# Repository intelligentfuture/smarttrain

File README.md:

# smarttrain
Software Project
- Conan
- Dome
- Neng
- Arm
- Ice
- Nami

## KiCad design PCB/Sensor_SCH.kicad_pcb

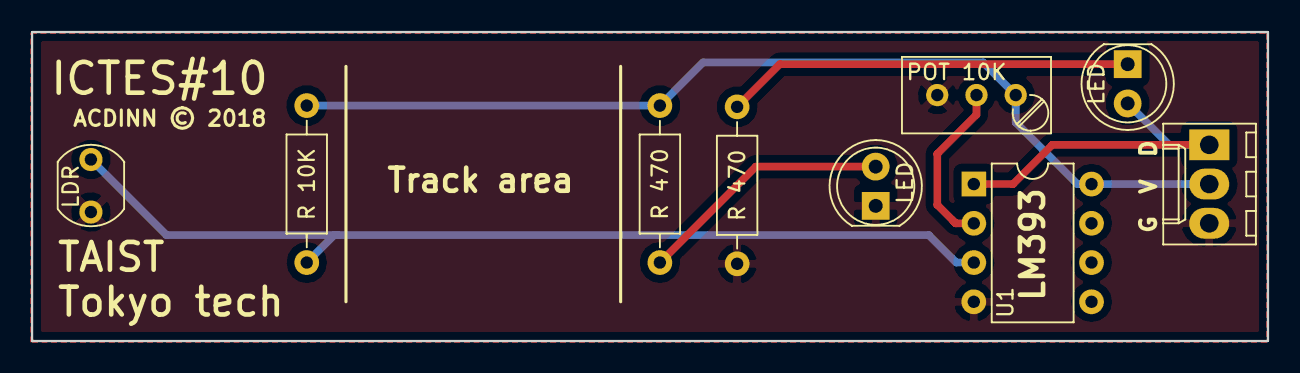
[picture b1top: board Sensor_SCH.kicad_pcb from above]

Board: 2 copper layers, 80.0 x 20.0 mm, 9 parts (0 on the bottom side), 7 nets.

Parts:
G  V  D: Conn_01x03; Molex_KK-6410-03_03x2.54mm_Straight
LDR: LDR07; Resistor_LDR_5.1x4.3_RM3.4
LED: LED; LED_D5.0mm
LED#2: LED; LED_D5.0mm
POT 10K: POT; Potentiometer_Trimmer_Bourns_3296W
R 10K, R 470, R 470#2: R; R_Axial_DIN0207_L6.3mm_D2.5mm_P10.16mm_Horizontal
U1: LM393; DIP-8_W7.62mm

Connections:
/Data: G V D.1, LED#2.2, U1.1
/GND: G V D.3, LDR.2, LED.1, POT 10K.3, R 470#2.2, U1.4
/Vcc: G V D.2, POT 10K.1, R 10K.1, R 470.1, U1.8
unnamed: LED.2, R 470.2
unnamed: LED#2.1, R 470#2.1
unnamed: LDR.1, R 10K.2
unnamed: POT 10K.2, U1.2

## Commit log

2018-03-19 init project
2018-03-19 update multipoll
2018-03-19 change boardrate
2018-03-19 remove empty line
2018-03-19 change debug msg
2018-03-19 update store
2018-03-19 change updateDB to multinode support
2018-03-19 add while to call updateDB()
2018-03-19 updateDB() -json dumps before sending
2018-03-19 clean print
2018-03-20 multiple node reader
2018-03-20 printout modbus
2018-03-20 check modbus
2018-03-20 change brate to 57600
2018-03-20 change read method for RS485
2018-03-20 print resp at update
2018-03-26 update many things, much more than i can remember, haha
2018-03-26 add sourcecode of mbed
2018-03-26 update store.py, add service /api/active , /api/timetable and /api/seed
2018-03-27 organize files
2018-04-18 Add PCB file
2018-04-18 add arduino ESP code for station node
2018-04-18 add micropython ESP code for gateway node
2018-04-18 commit before sleep
2018-04-19 FIX bug, improve performance, and more hidden bug.
2018-04-21 make data to dict
2018-04-25 Initial v2 with NTP include in each node
2018-04-25 add files
2018-04-25 ESP8266 with NTP sync
2018-04-25 update GW
2018-04-27 change esp to 6 pin and many many many fix
2018-04-28 remove delay
2018-04-28 add timetable calculator
2018-04-28 add example files .list
2018-04-30 edit node
2018-04-30 thread test
2018-04-30 add caltimetable
2018-04-30 add socket shutdown
2018-05-01 add calculate table (cal22.py)
2018-05-01 add timetable service
2018-05-01 change pin order
2018-05-01 update order
2018-05-01 clean comment
2018-05-01 call function from another file
2018-05-01 add TrainController
2018-05-01 add init system
2018-05-01 test init system
2018-05-01 add test
2018-05-01 update init system
2018-05-02 update set timetable
2018-05-02 send speed to server
2018-05-02 add Request library
2018-05-03 try ticker
2018-05-03 fix missing name
2018-05-03 small fix
2018-05-03 show dist(a,b)
2018-05-03 change function
2018-05-03 update speed control
2018-05-03 update from universe
2018-05-04 include example files for values
2018-05-04 update test
2018-05-04 set experiments
2018-05-04 init experiment but running state is incorrect
2018-05-04 rollback TrainController
2018-05-04 rollback
2018-05-04 clear files
2018-05-04 fix swap value
2018-05-04 update collect sensors
2018-05-04 update collect sensors-filter false values
2018-05-04 update collect sensors-filter update timestamp
2018-05-04 update anything
2018-05-04 edit test
2018-05-04 edit permission
2018-05-04 add generate-timetable.py
2018-05-04 test gen tbl
2018-05-04 fix merge
2018-05-04 add new file
2018-05-04 adaptive timetable generator v0.1
2018-05-05 update timetable generator
2018-05-05 add file sensors and distab
2018-05-05 add logging

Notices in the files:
PCB/Sensor_SCH.kicad_pcb:
ACDINN © 2018
